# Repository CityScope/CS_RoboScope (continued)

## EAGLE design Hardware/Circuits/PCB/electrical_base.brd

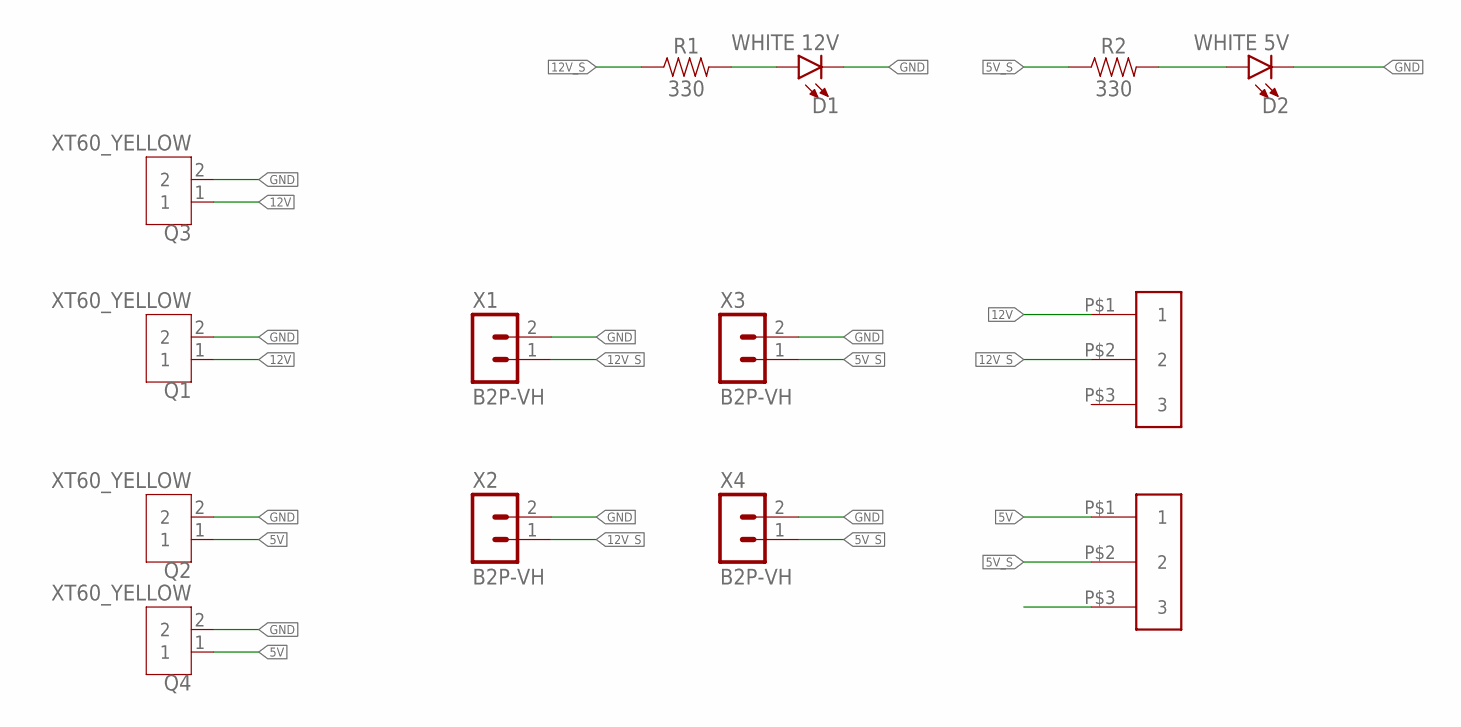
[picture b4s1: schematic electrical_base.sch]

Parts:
D1: WHITE 12V; LED-1206
D2: WHITE 5V; LED-1206
Q1, Q2, Q3, Q4: XT60_YELLOW; AMASS_XT60PB-M
R1, R2: 330; 0603
U$1, U$2: SWITCH_3P_4.7; 3P
X1, X2, X3, X4: B2P-VH

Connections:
5V: Q2.1, Q4.1, U$2.P$1 (1)
5V_S: R2.1, U$2.P$2 (2), X3.1, X4.1
12V: Q1.1, Q3.1, U$1.P$1 (1)
12V_S: R1.1, U$1.P$2 (2), X1.1, X2.1
GND: D1.C, D2.C, Q1.2, Q2.2, Q3.2, Q4.2, X1.2, X2.2, X3.2, X4.2
unnamed: D1.A, R1.2
unnamed: D2.A, R2.2

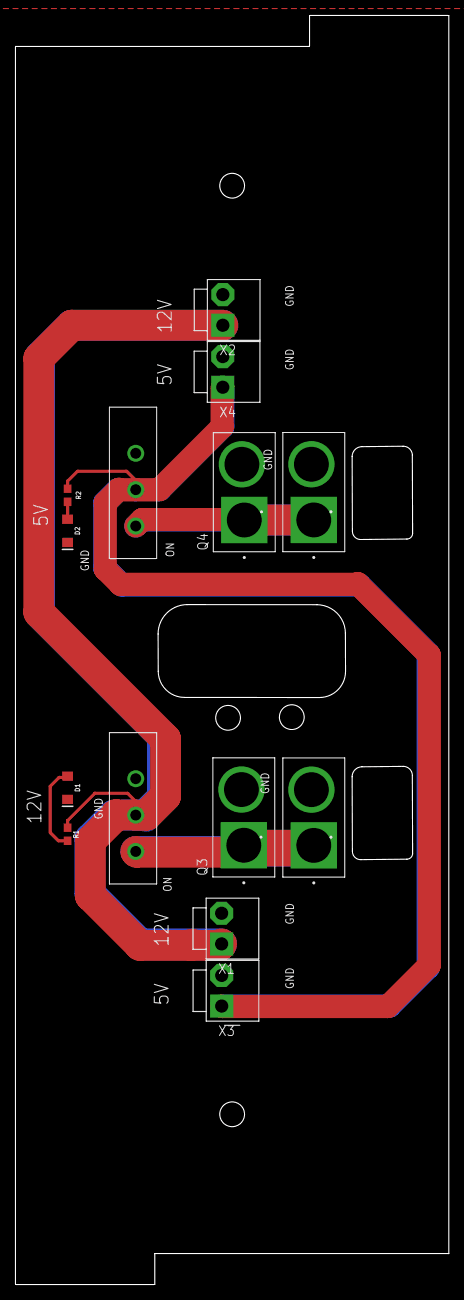
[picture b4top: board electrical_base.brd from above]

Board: 2 copper layers, 56.0 x 164.0 mm, 14 parts (0 on the bottom side), 7 nets.

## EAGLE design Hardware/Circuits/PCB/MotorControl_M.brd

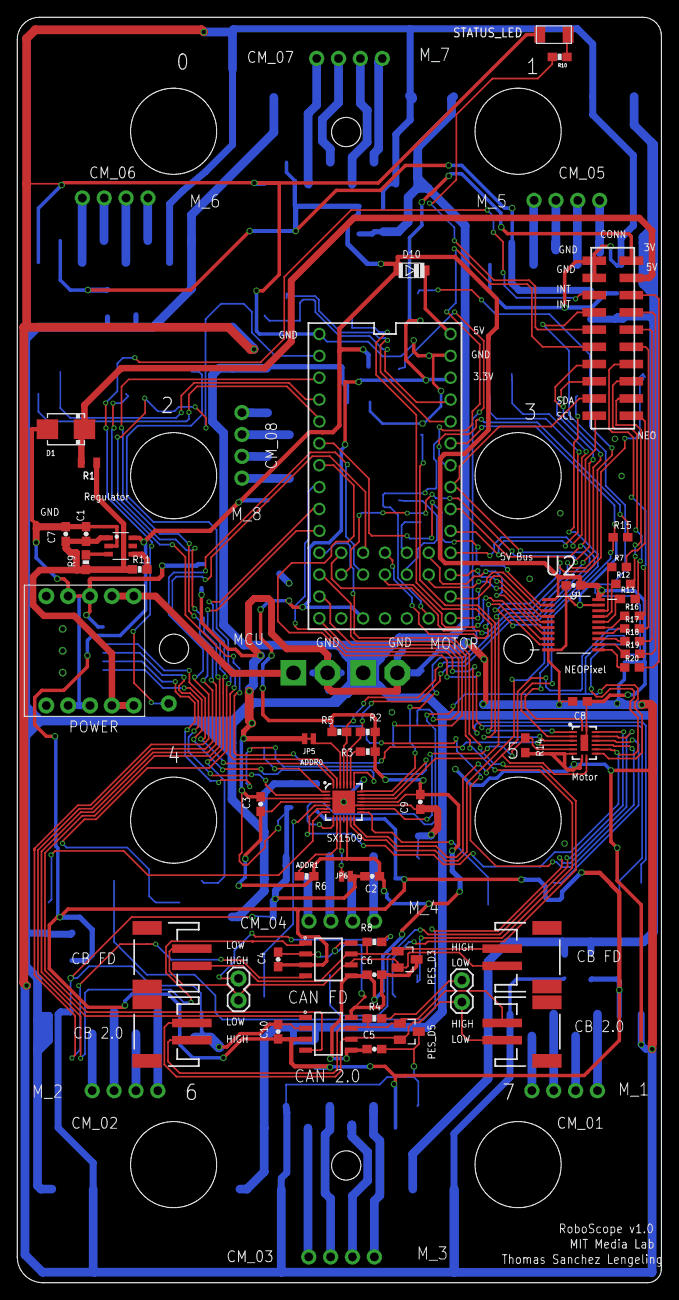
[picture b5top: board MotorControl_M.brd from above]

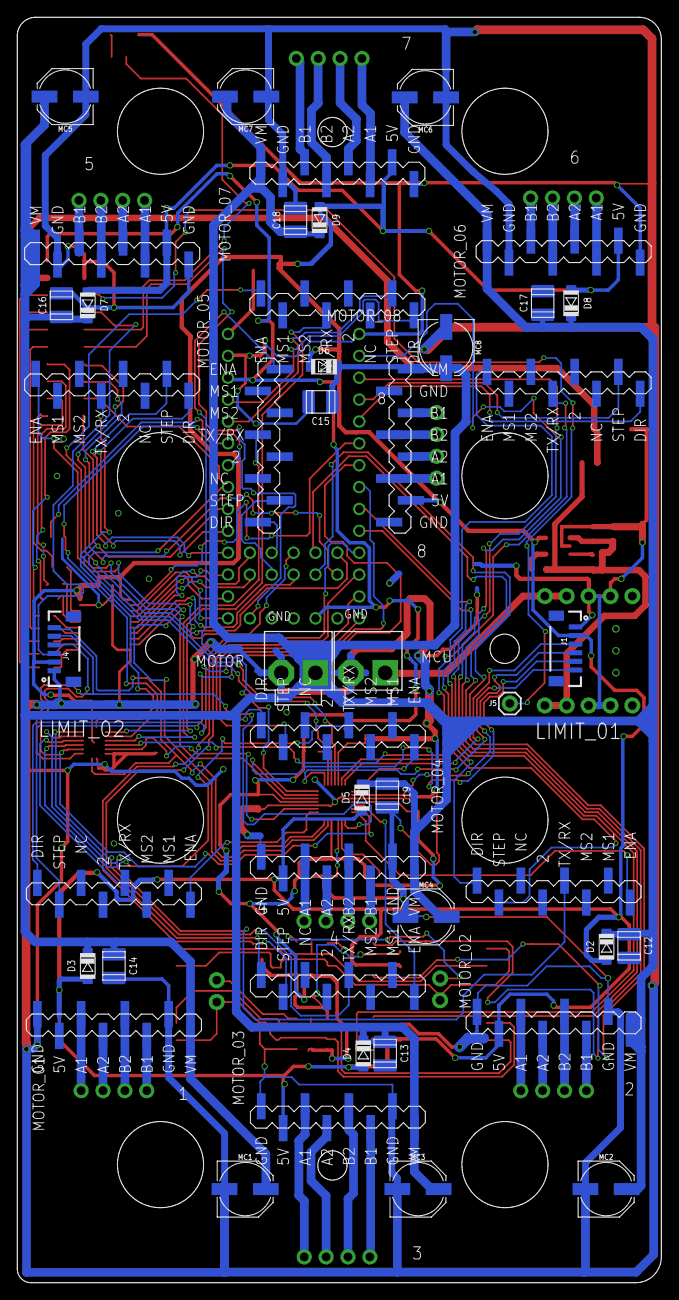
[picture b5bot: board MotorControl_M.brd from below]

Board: 2 copper layers, 74.8 x 147.0 mm, 99 parts (37 on the bottom side), 131 nets.

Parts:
C1: 47uf/10V; 0603-CAP
C2, C3, C9: 0.1uF; 0603-CAP
C4, C5, C6, C7, C10: 0.1uf; 0603-CAP
C8: 0.1uF; 0603
C11: 1uf; 0603-CAP
C12: 10uf; C1210
C13, C14, C15, C16, C17, C18, C19: C1210
CAN_INPUT, CAN_INPUT1, CAN_INPUT4, CAN_INPUT5: JST-2-SMD
CM_01, CM_02, CM_03, CM_04, CM_05, CM_06, CM_07, CM_08: 1X04_STRAIGHT; 1X04-CLEANBIG
D1: S2A; DO214AA
D2, D3, D4, D5, D6, D7, D8, D9: SOD123
D10: SOD123L; SOD123
DRILEGEND: DRILEGEND
J1, J4: 1X06-1MM
J2, J3: 1X02
J5: 1X01
JP5, JP6: JUMPER-SMT_2_NC_TRACE_NO-SILK; SMT-JUMPER_2_NC_TRACE_NO-SILK
MC1, MC2, MC3, MC4, MC5, MC6, MC7, MC8: 100uF; PANASONIC_D
MCP2562FD, MCP2562_2.0: MCP2562-E/SN; SOIC127P600X175-8N
MOTOR_01, MOTOR_02, MOTOR_03, MOTOR_04, MOTOR_05, MOTOR_06, MOTOR_07, MOTOR_08: DRV8880TMC2209; TMC2209_SMD
P1: M-2X10-87759; 87759-20
PES_D3, PES_D5: PESD1CAN; SOT23
POWER_M: B2P-VH
POWER_MCU: B2P-VH
R1: 0.3; 0805
R2, R3, R5, R6, R9, R11: 10K; 0603-RES
R4, R8: 120; 0603-RES
R7, R12, R13, R16, R17, R18, R19, R20: 100; 0603
R10: 500; 0603-RES
R14: 10k; 0603
R15: 1k; 0603
STATUS_LED: LEDFAB1206; LED1206FAB
SX1509: SX1509; QFN-28
U1: MIC2005; SOT23-6
U2: 74HCT245D,65220-TSSOP; 20-TSSOP
U4: 74HC4051BQ; DHVQFN-16-2.5X3.5MM
U$1: MOSFET_SLIDER
U$3: TEENSY_4.0_WITH_SMD_HEADER_PINS

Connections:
3.3V: C2.1, C3.1, C5.1, C6.1, C9.1, MCP2562FD.5, MCP2562_2.0.5, P1.19, R2.2, R3.2, R5.2, R6.2, SX1509.4, SX1509.12, SX1509.18, U$3.3.3V, U$3.3.3V1
!RESET: R3.1, SX1509.23
CAN_H: CAN_INPUT.1, CAN_INPUT1.1, MCP2562FD.7, PES_D3.1, R8.1
CAN_H2: CAN_INPUT4.1, CAN_INPUT5.1, MCP2562_2.0.7, PES_D5.1, R4.1
CAN_L: CAN_INPUT.2, CAN_INPUT1.2, J2.2, MCP2562FD.6, PES_D3.2
CAN_L2: CAN_INPUT4.2, CAN_INPUT5.2, J3.2, MCP2562_2.0.6, PES_D5.2
CAN_RX2: MCP2562_2.0.4, U$3.0
CAN_RX3: MCP2562FD.4, U$3.30
CAN_TX2: MCP2562_2.0.1, U$3.1
CAN_TX3: MCP2562FD.1, U$3.31
GND_MCU: C1.2, C2.2, C3.2, C4.2, C5.2, C6.2, C7.2, C8.2, C9.2, C10.2, C11.2, C12.1, C13.1, C14.1, C15.1, C16.1, C17.1, C18.1, C19.1, D1.A, J1.1, J4.1, JP5.2, JP6.1, MC1.-, MC2.-, MC3.-, MC4.-, MC5.-, MC6.-, MC7.-, MC8.-, MCP2562FD.2, MCP2562FD.8, MCP2562_2.0.2, MCP2562_2.0.8, MOTOR_01.GND_0, MOTOR_01.GND_1, MOTOR_02.GND_0, MOTOR_02.GND_1, MOTOR_03.GND_0, MOTOR_03.GND_1, MOTOR_04.GND_0, MOTOR_04.GND_1, MOTOR_05.GND_0, MOTOR_05.GND_1, MOTOR_06.GND_0, MOTOR_06.GND_1, MOTOR_07.GND_0, MOTOR_07.GND_1, MOTOR_08.GND_0, MOTOR_08.GND_1, P1.18, P1.20, PES_D3.3, PES_D5.3, POWER_M.2, POWER_MCU.2, R14.2, STATUS_LED.2, SX1509.3, SX1509.17, SX1509.29, U1.2, U2.10, U2.19, U4.7, U4.8, U$1.GND_1, U$1.GND_2, U$1.GND_3, U$1.GND_4, U$3.GND, U$3.GND1, U$3.GND2
INPUT_01: J5.1, P1.16
INPUT_02: J4.3, P1.14
INT_00: R6.1, SX1509.9
INT_01: P1.6, U$3.32
INT_02: P1.8, U$3.33
MA1_01: CM_01.1, MOTOR_01.A1
MA1_02: CM_02.1, MOTOR_02.A1
MA1_03: CM_03.1, MOTOR_03.A1
MA1_04: CM_04.1, MOTOR_04.A1
MA1_05: CM_05.1, MOTOR_05.A1
MA1_06: CM_06.1, MOTOR_06.A1
MA1_07: CM_07.1, MOTOR_07.A1
MA1_08: CM_08.1, MOTOR_08.A1
MA2_01: CM_01.2, MOTOR_01.A2
MA2_02: CM_02.2, MOTOR_02.A2
MA2_03: CM_03.2, MOTOR_03.A2
MA2_04: CM_04.2, MOTOR_04.A2
MA2_05: CM_05.2, MOTOR_05.A2
MA2_06: CM_06.2, MOTOR_06.A2
MA2_07: CM_07.2, MOTOR_07.A2
MA2_08: CM_08.2, MOTOR_08.A2
MB1_01: CM_01.4, MOTOR_01.B1
MB1_02: CM_02.4, MOTOR_02.B1
MB1_03: CM_03.4, MOTOR_03.B1
MB1_04: CM_04.4, MOTOR_04.B1
MB1_05: CM_05.4, MOTOR_05.B1
MB1_06: CM_06.4, MOTOR_06.B1
MB1_07: CM_07.4, MOTOR_07.B1
MB1_08: CM_08.4, MOTOR_08.B1
MB2_01: CM_01.3, MOTOR_01.B2
MB2_02: CM_02.3, MOTOR_02.B2
MB2_03: CM_03.3, MOTOR_03.B2
MB2_04: CM_04.3, MOTOR_04.B2
MB2_05: CM_05.3, MOTOR_05.B2
MB2_06: CM_06.3, MOTOR_06.B2
MB2_07: CM_07.3, MOTOR_07.B2
MB2_08: CM_08.3, MOTOR_08.B2
MDIR_01: MOTOR_01.DIR, U$3.6
MDIR_02: MOTOR_02.DIR, U$3.8
MDIR_03: MOTOR_03.DIR, U$3.10
MDIR_04: MOTOR_04.DIR, U$3.12
MDIR_05: MOTOR_05.DIR, U$3.17/A3
MDIR_06: MOTOR_06.DIR, U$3.3
MDIR_07: MOTOR_07.DIR, U$3.23/A9
MDIR_08: MOTOR_08.DIR, U$3.27
MOTOR_MUX_RX: R15.1, U4.3, U$3.21/A7
MOTOR_MUX_TX: R15.2, U$3.20/A6
MOTOR_TX_RX_01: MOTOR_01.TX/RX, U4.13
MOTOR_TX_RX_02: MOTOR_02.TX/RX, U4.14
MOTOR_TX_RX_03: MOTOR_03.TX/RX, U4.15
MOTOR_TX_RX_04: MOTOR_04.TX/RX, U4.12
MOTOR_TX_RX_05: MOTOR_05.TX/RX, U4.1
MOTOR_TX_RX_06: MOTOR_06.TX/RX, U4.5
MOTOR_TX_RX_07: MOTOR_07.TX/RX, U4.2
MOTOR_TX_RX_08: MOTOR_08.TX/RX, U4.4
MSTEP_01: MOTOR_01.STEP, U$3.5
MSTEP_02: MOTOR_02.STEP, U$3.7
MSTEP_03: MOTOR_03.STEP, U$3.9
MSTEP_04: MOTOR_04.STEP, U$3.11
MSTEP_05: MOTOR_05.STEP, U$3.16/A2
MSTEP_06: MOTOR_06.STEP, U$3.2
MSTEP_07: MOTOR_07.STEP, U$3.22/A8
MSTEP_08: MOTOR_08.STEP, U$3.26
unnamed: J2.1, R8.2
unnamed: J3.1, R4.2
unnamed: D10.C, U$3.VIN
unnamed: R7.1, U2.18
unnamed: R12.1, U2.17
unnamed: R13.1, U2.16
unnamed: R11.2, U1.4
unnamed: R16.1, U2.15
unnamed: R17.1, U2.14
unnamed: R9.2, U1.3
unnamed: R18.1, U2.13
unnamed: R19.1, U2.12
unnamed: R20.1, U2.11
unnamed: R10.1, STATUS_LED.1
NEOPIXEL_01_3V: U2.2, U$3.4
NEOPIXEL_01_5V: P1.1, R7.2
NEOPIXEL_02_3V: U2.3, U$3.13
NEOPIXEL_02_5V: P1.3, R12.2
NEOPIXEL_03_3V: U2.4, U$3.14/A0
NEOPIXEL_03_5V: P1.5, R13.2
NEOPIXEL_04_3V: U2.5, U$3.15/A1
NEOPIXEL_04_5V: P1.7, R16.2
NEOPIXEL_05_3V: U2.6, U$3.24
NEOPIXEL_05_5V: P1.9, R17.2
NEOPIXEL_06_3V: U2.7, U$3.25
NEOPIXEL_06_5V: P1.11, R18.2
NEOPIXEL_07_3V: U2.8, U$3.28
NEOPIXEL_07_5V: P1.13, R19.2
NEOPIXEL_08_3V: U2.9, U$3.29
NEOPIXEL_08_5V: P1.15, R20.2
RESET: P1.10, U$3.RESET
STATUS_PIN: P1.12, R10.2
SX00_0: MOTOR_06.ENA, SX1509.27
SX00_1: J1.3, SX1509.28
SX00_2: MOTOR_04.ENA, SX1509.1
SX00_3: J1.4, SX1509.2
SX00_4: MOTOR_03.ENA, SX1509.5
SX00_5: J4.4, SX1509.6, U4.11
SX00_6: MOTOR_02.ENA, SX1509.7
SX00_7: J4.5, SX1509.8, U4.10
SX00_8: MOTOR_05.ENA, SX1509.13
SX00_9: J4.6, SX1509.14, U4.9
SX00_10: MOTOR_01.ENA, SX1509.15
SX00_11: R14.1, SX1509.16, U4.6
SX00_12: MOTOR_07.ENA, SX1509.19
SX00_13: J1.5, SX1509.20
SX00_14: MOTOR_08.ENA, SX1509.21
SX00_15: J1.6, SX1509.22
SX00_ADDR0: JP5.1, SX1509.26
SX00_ADDR1: JP6.2, SX1509.10
SX00_SCL: P1.4, R5.1, SX1509.25, U$3.19/A5
SX00_SDA: P1.2, R2.1, SX1509.24, U$3.18/A4
VCC_5VREG: C4.1, C8.1, C10.1, C11.1, D2.A, D3.A, D4.A, D5.A, D6.A, D7.A, D8.A, D9.A, D10.A, J1.2, J4.2, MCP2562FD.3, MCP2562_2.0.3, MOTOR_01.5V, MOTOR_02.5V, MOTOR_03.5V, MOTOR_04.5V, MOTOR_05.5V, MOTOR_06.5V, MOTOR_07.5V, MOTOR_08.5V, U1.6, U2.1, U2.20, U4.16, U4.EP
VCC_LEDS: D1.C, P1.17, R1.1
VCC_M: C12.2, C13.2, C14.2, C15.2, C16.2, C17.2, C18.2, C19.2, D2.C, D3.C, D4.C, D5.C, D6.C, D7.C, D8.C, D9.C, MC1.+, MC2.+, MC3.+, MC4.+, MC5.+, MC6.+, MC7.+, MC8.+, MOTOR_01.VM, MOTOR_02.VM, MOTOR_03.VM, MOTOR_04.VM, MOTOR_05.VM, MOTOR_06.VM, MOTOR_07.VM, MOTOR_08.VM, POWER_M.1
VCC_MCU: POWER_MCU.1, U$1.VIN_1, U$1.VIN_2
VCC_SWITCH: C1.1, C7.1, R1.2, R9.1, R11.1, U1.1, U$1.VOUT_1, U$1.VOUT_2

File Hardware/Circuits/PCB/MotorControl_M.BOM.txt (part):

Partlist exported from /Users/thomas/Documents/RoboScope/CS_RoboScope/Hardware/Circuits/PCB/MotorControl_M.sch at 1/24/21 11:08 PM

Qty Value                           Device                          Package                         Parts                                                                          Description                                                                                                     AVAILABILITY DESCRIPTION                          MF        MP           MPN OC_FARNELL OC_NEWARK PACKAGE        POPULARITY PRICE PROD_ID    PURCHASE-URL                                                  SF_ID     VALUE 
2                                   CONN_02                         1X02                            J2, J3                                                                         Multi connection point. Often used as Generic Header-pin footprint for 0.1 inch spaced/style header connections                                                                                                                                                                                                                            
4                                   CONN_02-JST-2MM-SMT             JST-2-SMD                       CAN_INPUT, CAN_INPUT1, CAN_INPUT4, CAN_INPUT5                                  Multi connection point. Often used as Generic Header-pin footprint for 0.1 inch spaced/style header connections                                                                                                                                   CONN-11443                                                                               
2                                   CONN_06SMD-1MM                  1X06-1MM                        J1, J4                                                                         Multi connection point. Often used as Generic Header-pin footprint for 0.1 inch spaced/style header connections                                                                                                                                   CONN-08249                                                               GPS-00579       
2   0.1uF                           0.1UF-0603-25V-(+80/-20%)       0603                            C8, C11                                                                        0.1µF ceramic capacitors                                                                                                                                                                                                                          CAP-00810                                                                          0.1uF 
3   0.1uF                           0.1UF-25V(+80/-20%)(0603)       0603-CAP                        C2, C3, C9                                                                     CAP-00810                                                                                                                                                                                                                                         CAP-00810                                                                          0.1uF 
5   0.1uf                           0.1UF-25V(+80/-20%)(0603)       0603-CAP                        C4, C5, C6, C7, C10                                                            CAP-00810                                                                                                                                                                                                                                         CAP-00810                                                                          0.1uF 
1   0.3                             0.3OHM-0805-1/8W-1%             0805                            R1                                                                             0.3Ω resistor                                                                                                                                                                                                                                     RES-11622                                                                          0.3   
1   100                             10KOHM-0603-1/10W-1%            0603                            R12                                                                            10kΩ resistor                                                                                                                                                                                                                                     RES-00824                                                                          10k   
8   100uF                           100UF-POLAR-25V-20%(ELEC)       PANASONIC_D                     MC1, MC2, MC3, MC4, MC5, MC6, MC7, MC8                                         100µF polarized capacitors                                                                                                                                                                                                                        CAP-12547                                                                          100uF 
1   10K                             0.3OHM-0805-1/8W-1%             0805                            R20                                                                            0.3Ω resistor                                                                                                                                                                                                                                     RES-11622                                                                          0.3   
1   10K                             10KOHM-0603-1/10W-1%            0603                            R13                                                                            10kΩ resistor                                                                                                                                                                                                                                     RES-00824                                                                          10k   
6   10K                             10KOHM-1/10W-1%(0603)0603       0603-RES                        R2, R3, R5, R6, R9, R11                                                        RES-00824                                                                                                                                                                                                                                         RES-00824                                                                          10K   
2   10k                             10KOHM-0603-1/10W-1%            0603                            R14, R15                                                                       10kΩ resistor                                                                                                                                                                                                                                     RES-00824                                                                          10k   
1   120                             10KOHM-1/10W-1%(0603)0603       0603-RES                        R8                                                                             RES-00824                                                                                                                                                                                                                                         RES-00824                                                                          10K   
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
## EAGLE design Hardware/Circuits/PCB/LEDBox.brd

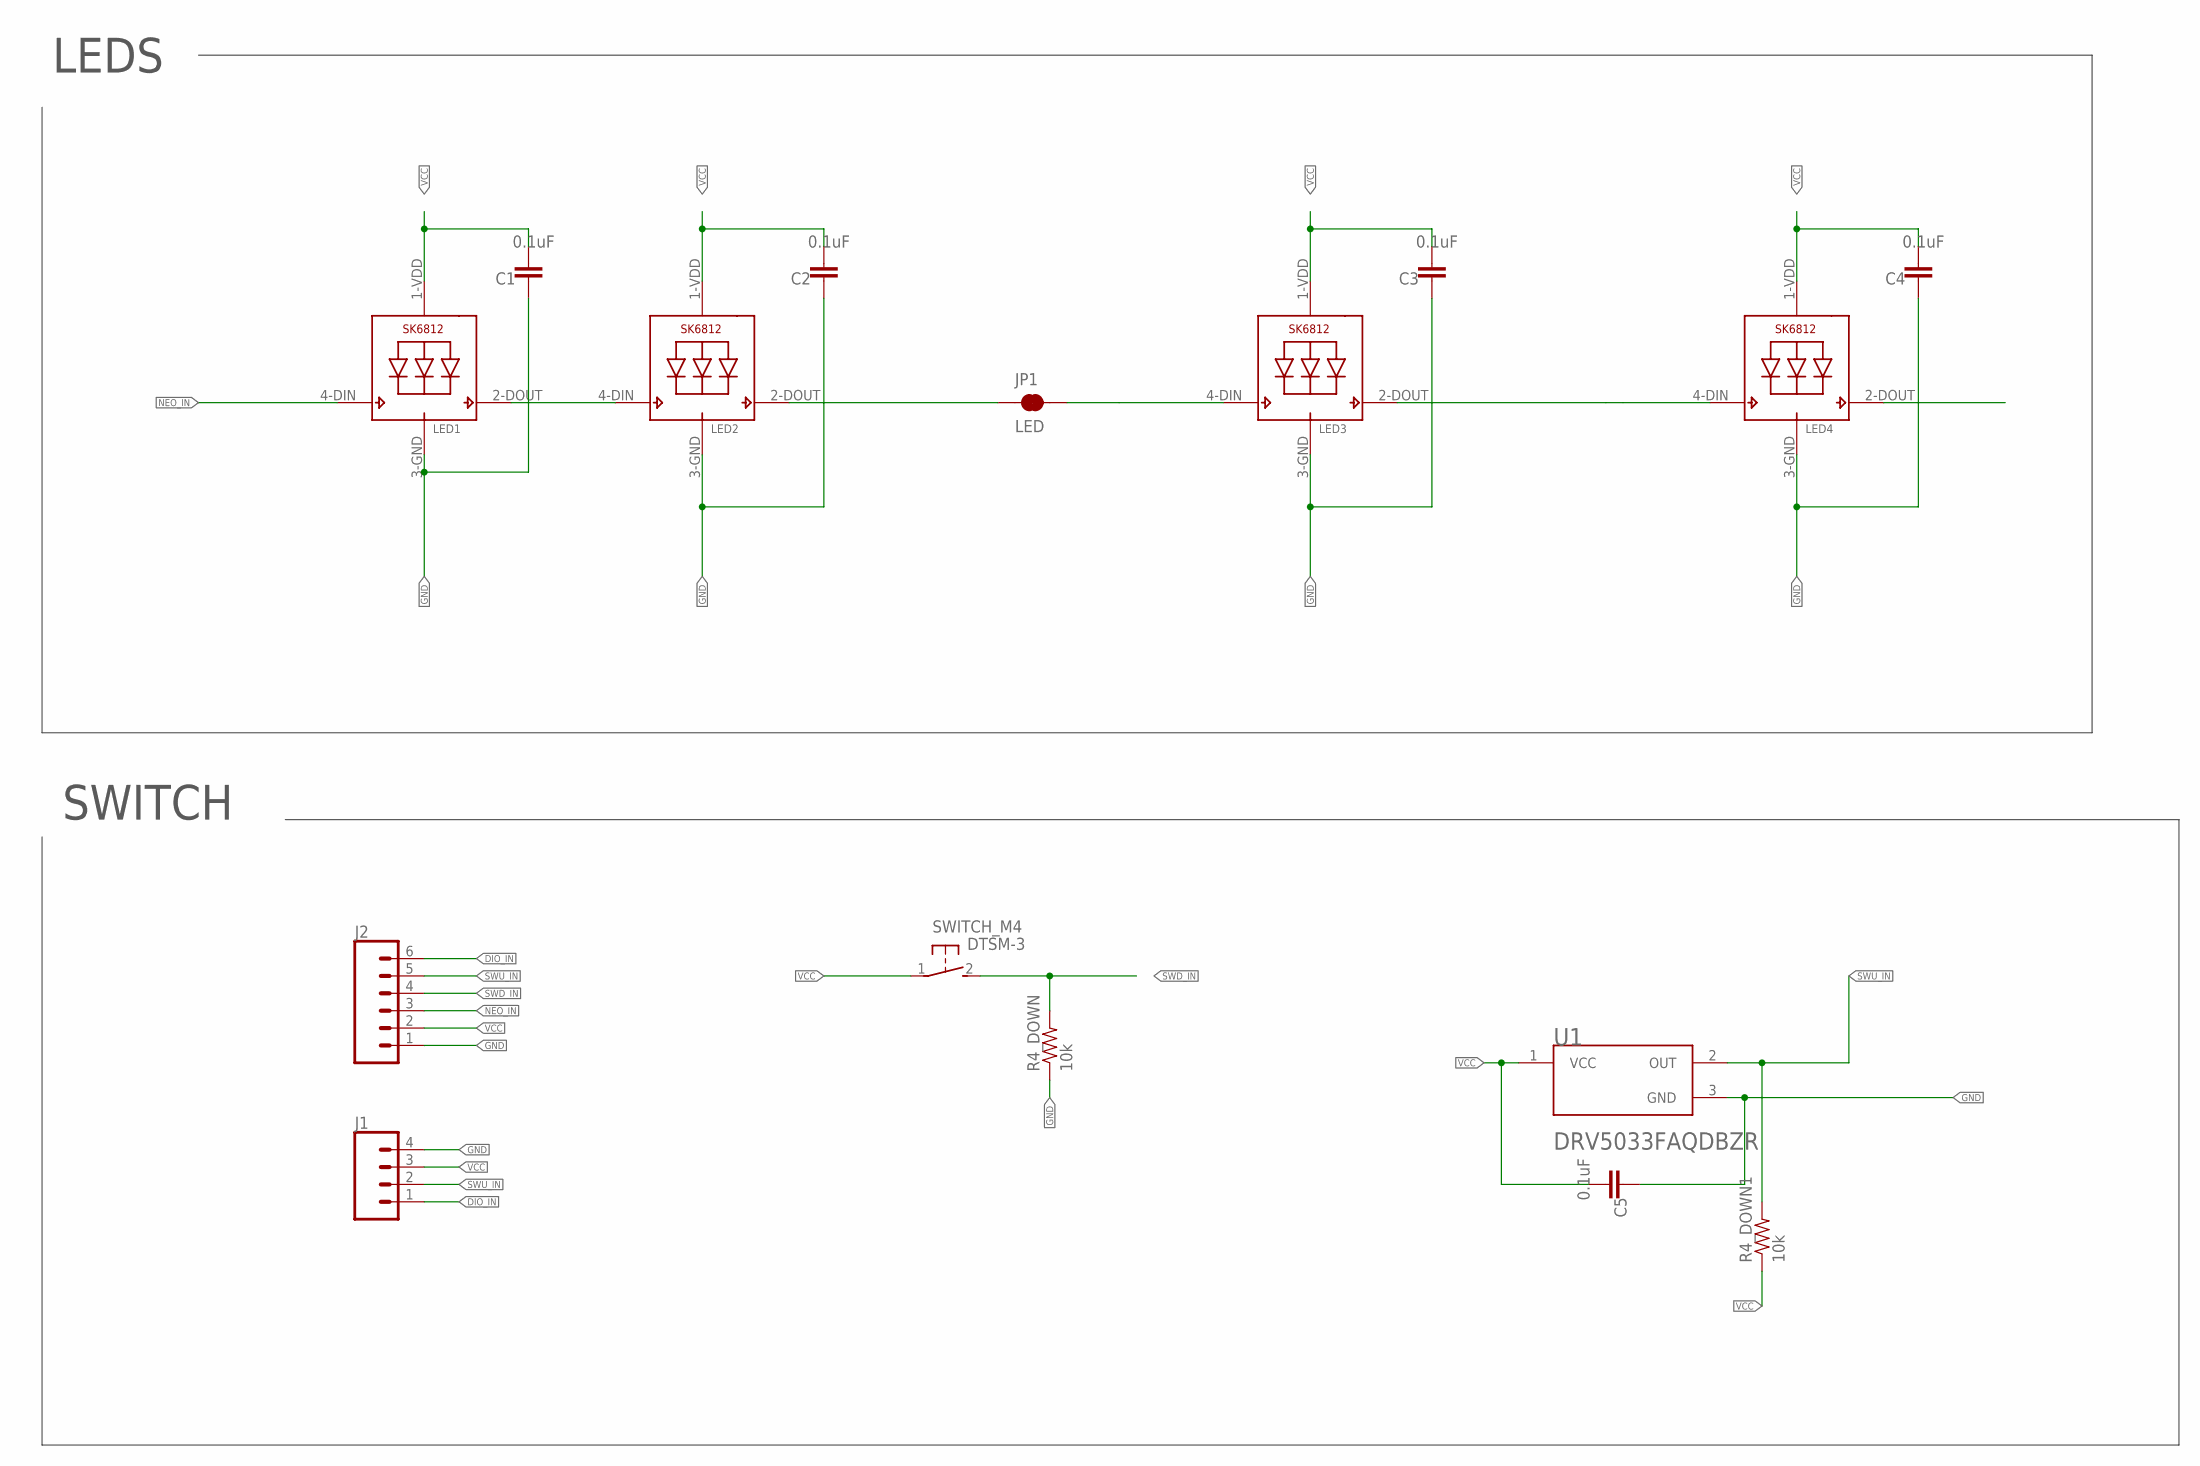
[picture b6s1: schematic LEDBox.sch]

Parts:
C1, C2, C3, C4, C5: 0.1uF; 0603
J1: CONN_041X04_NO_SILK; 1X04_NO_SILK
J2: CONN_06SMD-1MM; 1X06-1MM
JP1: LED; SMT-JUMPER_2_NC_TRACE_NO-SILK
LED1, LED2, LED3, LED4: SK6812_5050W; LED5050_W
R4_DOWN, R4_DOWN1: 10k; 0603
SWITCH_M4: DTSM-3
U1: TEXAS_INSTRUMENTS_DRV5033FAQDBZRTEXAS_INSTRUMENTS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; TEXAS_INSTRUMENTS_DRV5033FAQDBZR_0

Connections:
DIO_IN: J1.1, J2.6
GND: C1.1, C2.1, C3.1, C4.1, C5.1, J1.4, J2.1, LED1.3-GND (GND), LED2.3-GND (GND), LED3.3-GND (GND), LED4.3-GND (GND), R4_DOWN.1, U1.3 (GND)
unnamed: LED1.2-DOUT (DO), LED2.4-DIN (DI)
unnamed: JP1.1, LED2.2-DOUT (DO)
unnamed: JP1.2, LED3.4-DIN (DI)
unnamed: LED3.2-DOUT (DO), LED4.4-DIN (DI)
NEO_IN: J2.3, LED1.4-DIN (DI)
SWD_IN: J2.4, R4_DOWN.2, SWITCH_M4.2
SWU_IN: J1.2, J2.5, R4_DOWN1.2, U1.2 (OUT)
VCC: C1.2, C2.2, C3.2, C4.2, C5.2, J1.3, J2.2, LED1.1-VDD (VDD), LED2.1-VDD (VDD), LED3.1-VDD (VDD), LED4.1-VDD (VDD), R4_DOWN1.1, SWITCH_M4.1, U1.1 (VCC)

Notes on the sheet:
LEDS
SWITCH

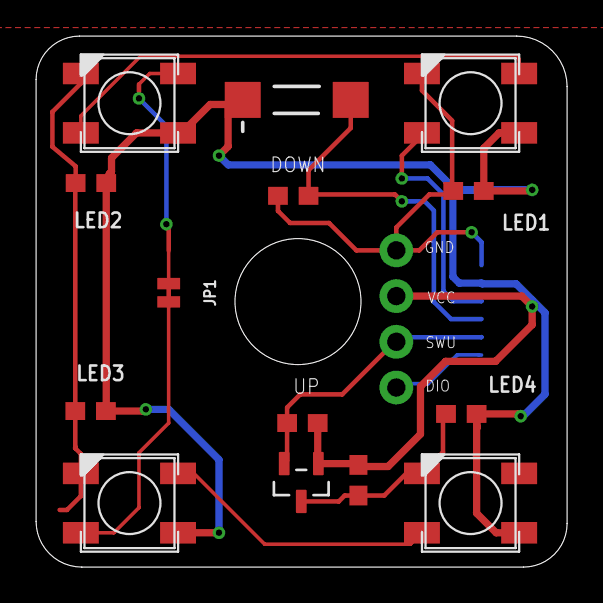
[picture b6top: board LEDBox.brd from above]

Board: 2 copper layers, 29.5 x 29.5 mm, 16 parts (1 on the bottom side), 10 nets.

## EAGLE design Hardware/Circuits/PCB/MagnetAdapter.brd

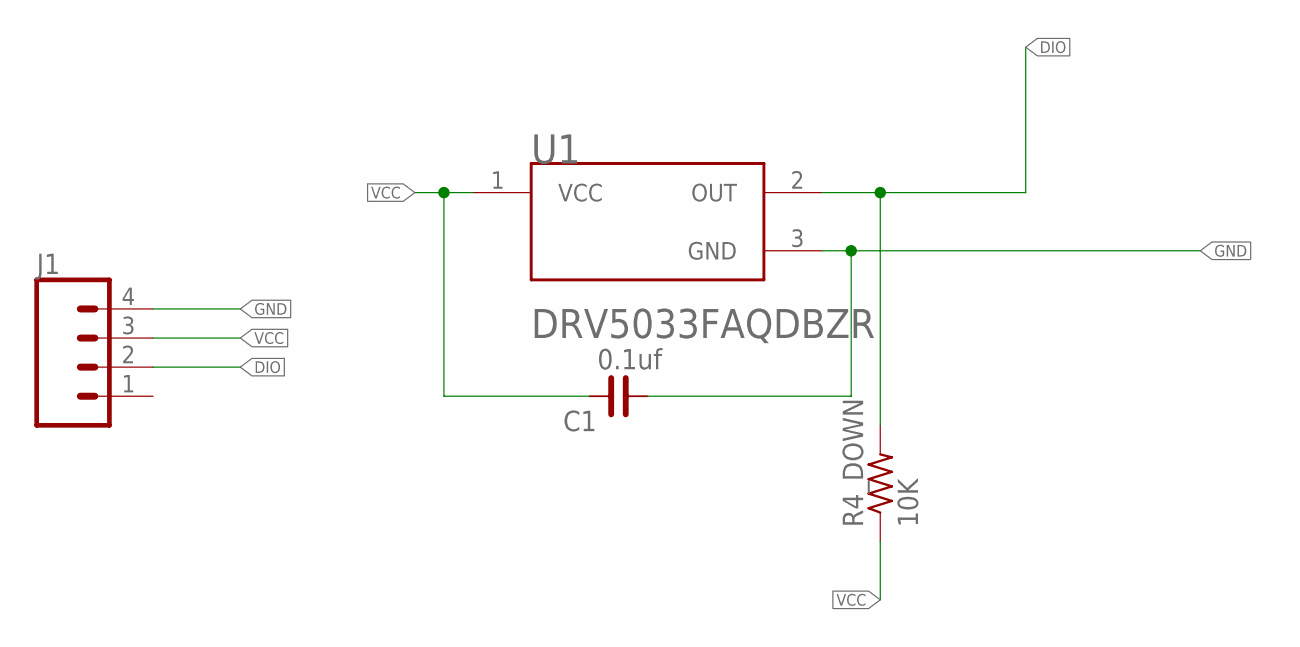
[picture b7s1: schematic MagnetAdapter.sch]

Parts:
C1: 0.1uf; C0805
J1: CONN_041X04_NO_SILK; 1X04_NO_SILK
R4_DOWN: 10K; M0805
U1: TEXAS_INSTRUMENTS_DRV5033FAQDBZRTEXAS_INSTRUMENTS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; TEXAS_INSTRUMENTS_DRV5033FAQDBZR_0

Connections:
DIO: J1.2, R4_DOWN.2, U1.2 (OUT)
GND: C1.1, J1.4, U1.3 (GND)
VCC: C1.2, J1.3, R4_DOWN.1, U1.1 (VCC)

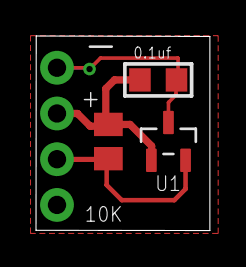
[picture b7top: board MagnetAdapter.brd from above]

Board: 2 copper layers, 9.7 x 10.8 mm, 4 parts (0 on the bottom side), 3 nets.

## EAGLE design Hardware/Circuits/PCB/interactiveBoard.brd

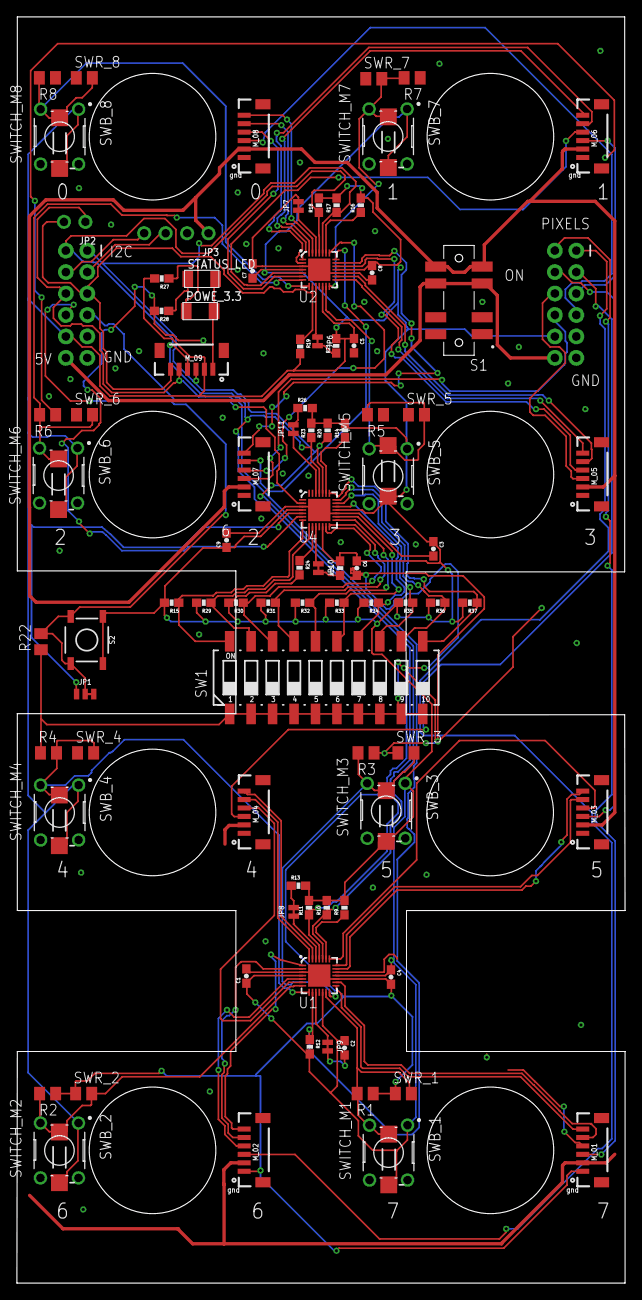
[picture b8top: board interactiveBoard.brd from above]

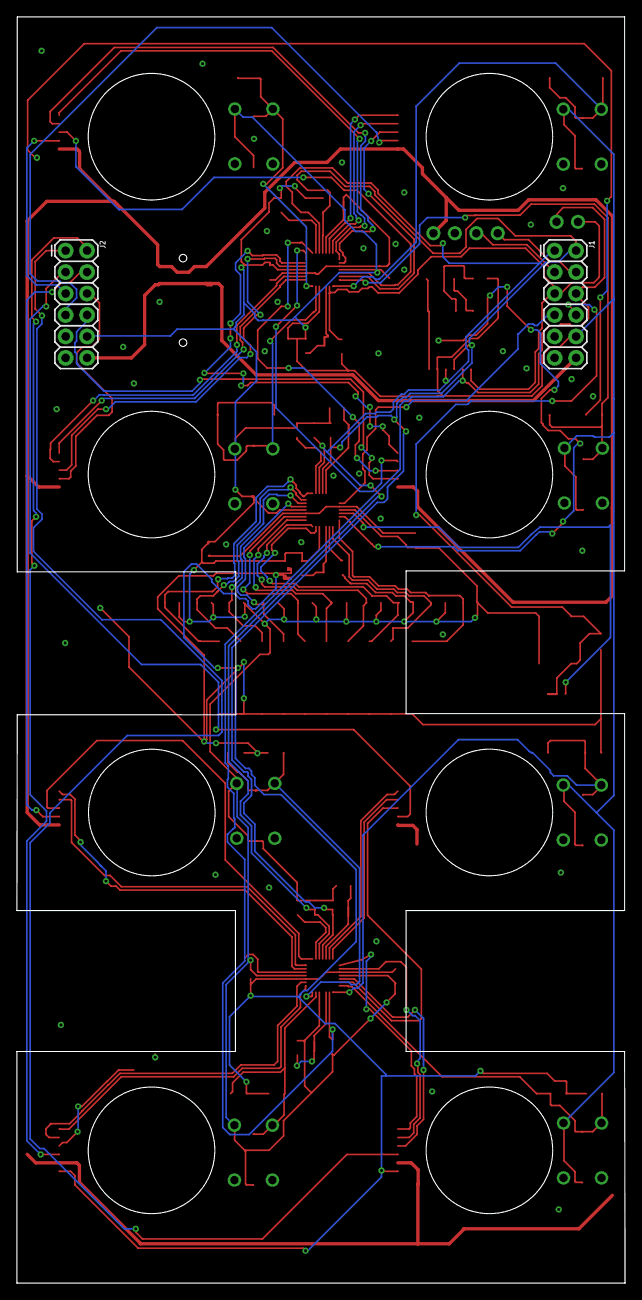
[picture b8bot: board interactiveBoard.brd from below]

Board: 2 copper layers, 72.0 x 149.9 mm, 98 parts (2 on the bottom side), 80 nets.

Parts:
C1, C2, C3, C4, C5, C6, C7, C8, C9: 0.1uF; 0603-CAP
J1, J2: 2X6 FEMALE; 2X6
JP1: JUMPER-SMT_3_1-NC_TRACE_NO-SILK; SMT-JUMPER_3_1-NC_TRACE_NO-SILK
JP2: 1X02_ROUND
JP3: 1X04_ROUND
JP6, JP7, JP8, JP9, JP10, JP11: JUMPER-SMT_2_NC_TRACE_NO-SILK; SMT-JUMPER_2_NC_TRACE_NO-SILK
M_01, M_02, M_03, M_04, M_05, M_06, M_07, M_08, M_09: 1X06-1MM
POWE_3.3: LEDFAB1206; LED1206FAB
R1, R2, R3, R5, R6, R7, R8: 10k; M0805
R4, R22: 10K; M0805
R9, R10, R11, R12, R13, R14, R15, R16, R17, R18, R19, R20, R21, R23, R24, R25, R26, R29, R30, R31, R32, R33, R34, R35, R36, R37: 10K; 0603-RES
R27, R28: 500; 0603-RES
S1: JS207011SCQNR; SW_JS207011SCQNR
S2: TACTILE_SWITCH_SMD_5.2MM
STATUS_LED: LEDFAB1206; LED1206FAB
SW1: 219-10; CTS-219-10
SWB_1, SWB_2, SWB_3, SWB_4, SWB_5, SWB_6, SWB_7, SWB_8: B3F-1000
SWITCH_M1, SWITCH_M2, SWITCH_M3, SWITCH_M4, SWITCH_M5, SWITCH_M6, SWITCH_M7, SWITCH_M8: DTSM-3
SWR_1, SWR_2, SWR_3, SWR_4, SWR_5, SWR_6, SWR_7, SWR_8: 10K; M0805
U1, U2, U4: SX1509; QFN-28

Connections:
0_SX1: M_04.6, U1.27
0_SX2: M_08.6, U2.27
1_SX1: M_04.5, U1.28
1_SX2: M_08.5, U2.28
2_SX1: M_02.6, U1.1
2_SX2: M_06.6, U2.1
3.3V: C1.1, C2.1, C3.1, C4.1, C5.1, C6.1, C7.1, C8.1, C9.1, J1.10, J2.10, M_09.2, R9.2, R10.2, R11.2, R12.2, R13.2, R14.2, R15.2, R16.2, R17.2, R18.2, R19.2, R20.2, R21.2, R23.2, R24.2, R25.2, R26.2, R27.2, R29.2, R30.2, R31.2, R32.2, R33.2, R34.2, R35.2, R36.2, R37.2, S2.1, S2.2, SWB_1.1, SWB_2.1, SWB_3.1, SWB_4.1, SWB_5.1, SWB_6.1, SWB_7.1, SWB_8.1, SWITCH_M1.1, SWITCH_M2.1, SWITCH_M3.1, SWITCH_M4.1, SWITCH_M5.1, SWITCH_M6.1, SWITCH_M7.1, SWITCH_M8.1, U1.4, U1.12, U1.18, U2.4, U2.12, U2.18, U4.4, U4.12, U4.18
3_SX1: M_02.5, U1.2
3_SX2: M_06.5, U2.2
3_SX3: J1.7, U4.2
4_SX1: M_02.4, U1.5
4_SX2: M_06.4, U2.5
4_SX3: JP1.1, U4.5
5_SX1: M_04.4, U1.6
5_SX2: M_08.4, U2.6
5_SX3: R28.2, U4.6
6_SX1: R2.2, SWB_2.3, SWITCH_M2.2, SWR_2.2, U1.7
6_SX2: R6.2, SWB_6.3, SWITCH_M6.2, SWR_6.2, U2.7
6_SX3: R15.1, SW1.20, U4.7
7_SX1: R4.2, SWB_4.3, SWITCH_M4.2, SWR_4.2, U1.8
7_SX2: R8.2, SWB_8.3, SWITCH_M8.2, SWR_8.2, U2.8
7_SX3: R29.1, SW1.19, U4.8
8_SX1: R1.2, SWB_1.3, SWITCH_M1.2, SWR_1.2, U1.13
8_SX2: R5.2, SWB_5.3, SWITCH_M5.2, SWR_5.2, U2.13
8_SX3: R30.1, SW1.18, U4.13
9_SX1: R3.2, SWB_3.3, SWITCH_M3.2, SWR_3.2, U1.14
9_SX2: R7.2, SWB_7.3, SWITCH_M7.2, SWR_7.2, U2.14
9_SX3: R31.1, SW1.17, U4.14
10_SX1: M_01.6, U1.15
10_SX2: M_05.6, U2.15
10_SX3: R32.1, SW1.16, U4.15
11_SX1: M_01.5, U1.16
11_SX2: M_05.5, U2.16
11_SX3: R33.1, SW1.15, U4.16
12_SX1: M_01.4, U1.19
12_SX2: M_05.4, U2.19
12_SX3: R34.1, SW1.14, U4.19
13_SX1: M_03.6, U1.20
13_SX2: M_07.6, U2.20
13_SX3: R35.1, SW1.13, U4.20
14_SX1: M_03.5, U1.21
14_SX2: M_07.5, U2.21
14_SX3: R36.1, SW1.12, U4.21
15_SX1: M_03.4, U1.22
15_SX2: M_07.4, U2.22
15_SX3: R37.1, SW1.11, U4.22
!INT_SX3: R24.1, U4.9
!RESET_SX1: R9.1, U1.23
!RESET_SX2: R16.1, U2.23
!RESET_SX3: R14.1, U4.23
ADDR0_SX1: JP8.1, U1.26
ADDR0_SX2: JP7.1, U2.26
ADDR0_SX3: JP11.1, U4.26
ADDR1_SX1: JP9.1, U1.10
ADDR1_SX2: JP6.1, U2.10
ADDR1_SX3: JP10.1, U4.10
CAN_RX2: J1.4, JP3.4
CAN_TX2: J1.3, JP3.3
GND_MCU: C1.2, C2.2, C3.2, C4.2, C5.2, C6.2, C7.2, C8.2, C9.2, J1.9, J1.11, J2.9, J2.11, JP3.2, JP7.2, JP9.2, M_01.1, M_02.1, M_03.1, M_04.1, M_05.1, M_06.1, M_07.1, M_08.1, M_09.1, POWE_3.3.2, R1.1, R2.1, R3.1, R4.1, R5.1, R6.1, R7.1, R8.1, R22.1, STATUS_LED.2, SW1.1, SW1.2, SW1.3, SW1.4, SW1.5, SW1.6, SW1.7, SW1.8, SW1.9, SW1.10, SWR_1.1, SWR_2.1, SWR_3.1, SWR_4.1, SWR_5.1, SWR_6.1, SWR_7.1, SWR_8.1, U1.3, U1.17, U1.29, U2.3, U2.17, U2.29, U4.3, U4.17, U4.29
INT_01: J1.6, JP2.1, M_09.5, R12.1, U1.9
INT_02: J1.5, JP2.2, M_09.6, R19.1, U2.9
unnamed: JP6.2, R21.1
unnamed: JP8.2, R13.1
unnamed: R28.1, STATUS_LED.1
unnamed: JP10.2, R25.1
unnamed: JP11.2, R26.1
unnamed: POWE_3.3.1, R27.1
NEOPIXEL_01: J2.2, M_01.3
NEOPIXEL_02: J2.1, M_02.3
NEOPIXEL_03: J2.4, M_03.3
NEOPIXEL_04: J2.3, M_04.3
NEOPIXEL_05: J2.6, M_05.3
NEOPIXEL_06: J2.5, M_06.3
NEOPIXEL_07: J2.8, M_07.3
NEOPIXEL_08: J2.7, M_08.3
RESET: J1.8, JP1.2, JP1.3, R22.2, S2.3, S2.4
SCL_00: J1.2, M_09.4, R11.1, R18.1, R23.1, U1.25, U2.25, U4.25
SDA_00: J1.1, M_09.3, R10.1, R17.1, R20.1, U1.24, U2.24, U4.24
VCC_5V: JP3.1, M_01.2, M_02.2, M_03.2, M_04.2, M_05.2, M_06.2, M_07.2, M_08.2, S1.4, S1.8
VCC_5V_IN: J1.12, J2.12, S1.3, S1.7
